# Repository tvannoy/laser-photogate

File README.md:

# Laser photogate

This is a laser photogate timing system, designed primarily for Science Olympiad events such as Wheeled Vehicle, Battery Buggy, Gravity Vehicle, etc.

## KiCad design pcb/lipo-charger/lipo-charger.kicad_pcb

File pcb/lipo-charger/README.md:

# Laser power supply hardware

[The KiCAD design files can be viewed online using KiCanvas.](https://kicanvas.org/?github=https%3A%2F%2Fgithub.com%2Ftvannoy%2Flaser-photogate%2Ftree%2Fhardware%2Fpcb%2Flipo-charger)

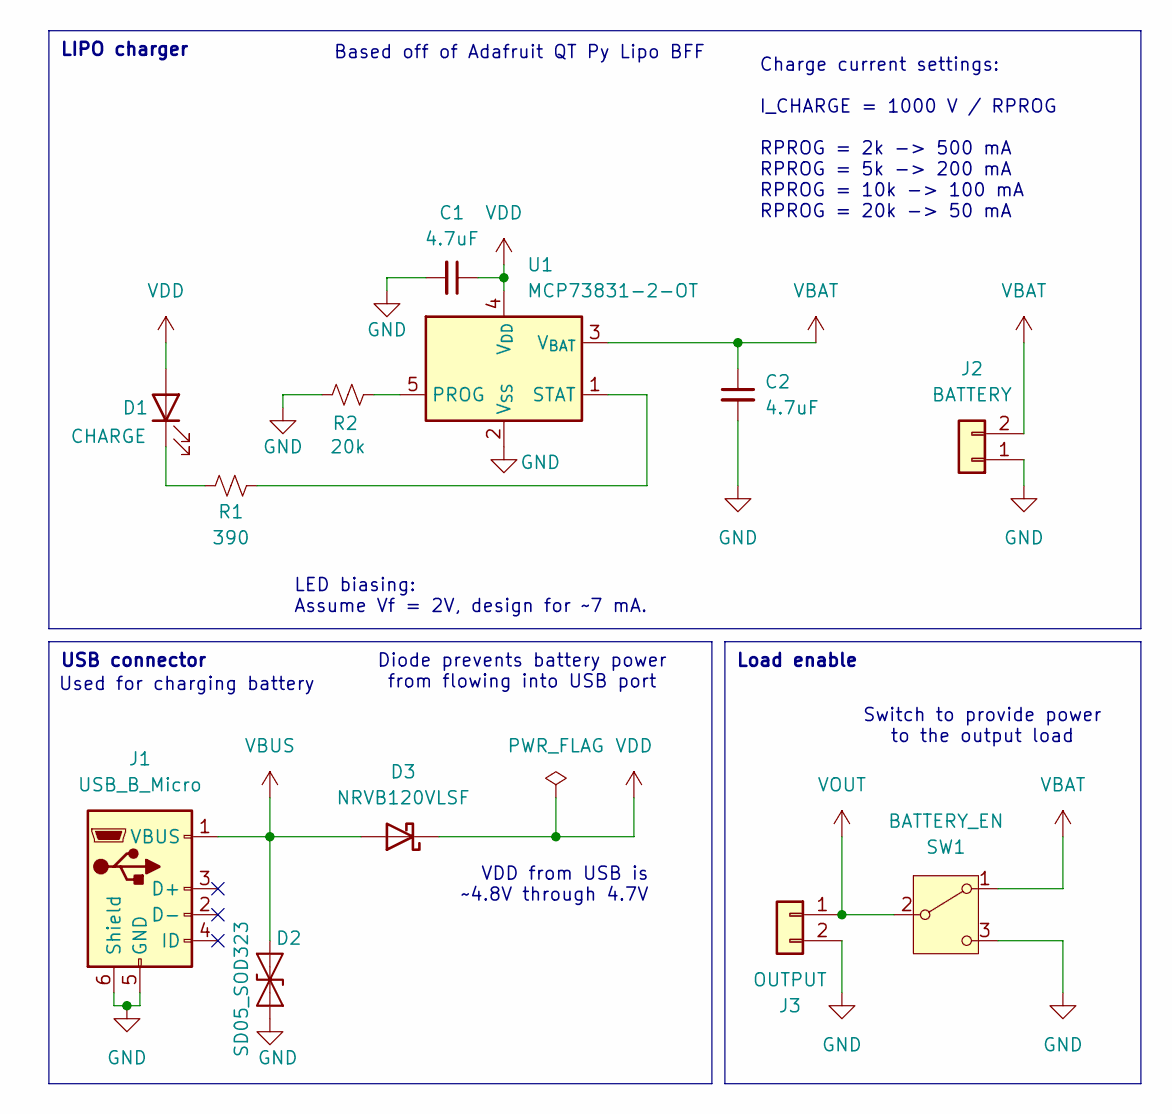
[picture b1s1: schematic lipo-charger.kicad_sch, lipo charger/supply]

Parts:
C1, C2: 4.7uF; C_0805_2012Metric_Pad1.18x1.45mm_HandSolder; Part Number CC0805KKX7R6BB475; JLC 0805
D1: CHARGE; LED_1206_3216Metric_Pad1.42x1.75mm_HandSolder; Part Number B1591UY--20C000112U1930; JLC 1206
D2: SD05_SOD323; D_SOD-323; Part Number Leiditech SD05; JLC SOD-323
D3: NRVB120VLSF; D_SOD-123F; Part Number SM5817PL-TP; JLC SOD-123FL
J1: USB_B_Micro; USB_Micro-B_Wuerth_629105150521; Part Number 629105150521
J2: BATTERY; JST_PH_B2B-PH-K_1x02_P2.00mm_Vertical; Part Number B2B-PH-K-S; JLCSC Part # C5251182
J3: OUTPUT; JST_PH_B2B-PH-K_1x02_P2.00mm_Vertical; Part Number B2B-PH-K-S; JLCSC Part # C5251182
R1: 390; R_0805_2012Metric_Pad1.20x1.40mm_HandSolder; Part Number RC0805FR-07390RL; JLC 0805
R2: 20k; R_0805_2012Metric_Pad1.20x1.40mm_HandSolder; Part Number RC0805FR-0720KL; JLC 0805
SW1: BATTERY_EN; SW_E-Switch_EG1224_SPDT_Angled; Part Number EG1224; JLCSC Part # C273395
U1: MCP73831-2-OT; SOT-23-5; Part Number MCP73831T-2ACI/OT; JLC SOT-23-5

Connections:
GND: C1.2, C2.2, D2.2 (A2), J1.5 (GND), J1.6 (Shield), J2.1, J3.2, R2.2, SW1.3 (C), U1.2 (V_{SS})
unnamed: D1.1 (K), R1.1
unnamed: R2.1, U1.5 (PROG)
unnamed: R1.2, U1.1 (STAT)
VBAT: C2.1, J2.2, SW1.1 (A), U1.3 (V_{BAT})
VBUS: D2.1 (A1), D3.2 (A), J1.1 (VBUS)
VDD: C1.1, D1.2 (A), D3.1 (K), U1.4 (V_{DD})
VOUT: J3.1, SW1.2 (B)

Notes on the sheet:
Load enable
USB connector
LIPO charger
VDD from USB is ~4.8V through 4.7V
Based off of Adafruit QT Py Lipo BFF
Charge current settings: I_CHARGE = 1000 V / RPROG RPROG = 2k -> 500 mA RPROG = 5k -> 200 mA RPROG = 10k -> 100 mA RPROG = 20k -> 50 mA
Diode prevents battery power from flowing into USB port
Used for charging battery
LED biasing: Assume Vf = 2V, design for ~7 mA.
Switch to provide power to the output load

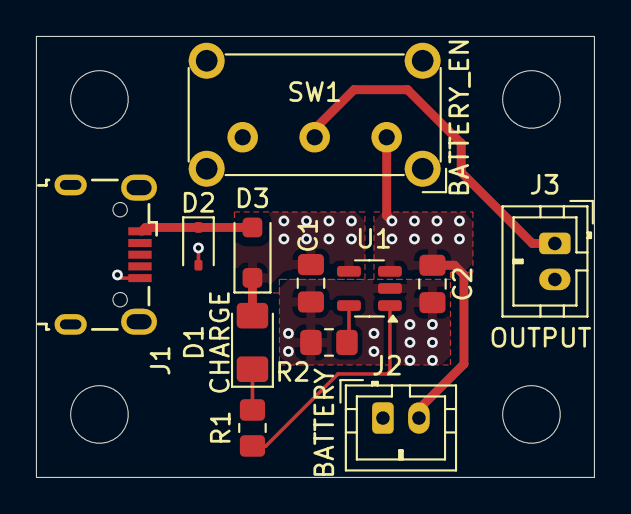
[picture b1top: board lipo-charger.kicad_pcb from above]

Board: 2 copper layers, 31.0 x 24.5 mm, 12 parts (0 on the bottom side), 8 nets.

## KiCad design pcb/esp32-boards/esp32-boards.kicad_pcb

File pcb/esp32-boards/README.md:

# ESP32 wireless photogate hardware

[The KiCAD design files can be viewed online using KiCanvas.](https://kicanvas.org/?github=https%3A%2F%2Fgithub.com%2Ftvannoy%2Flaser-photogate%2Ftree%2Fhardware%2Fpcb%2Fesp32-boards)

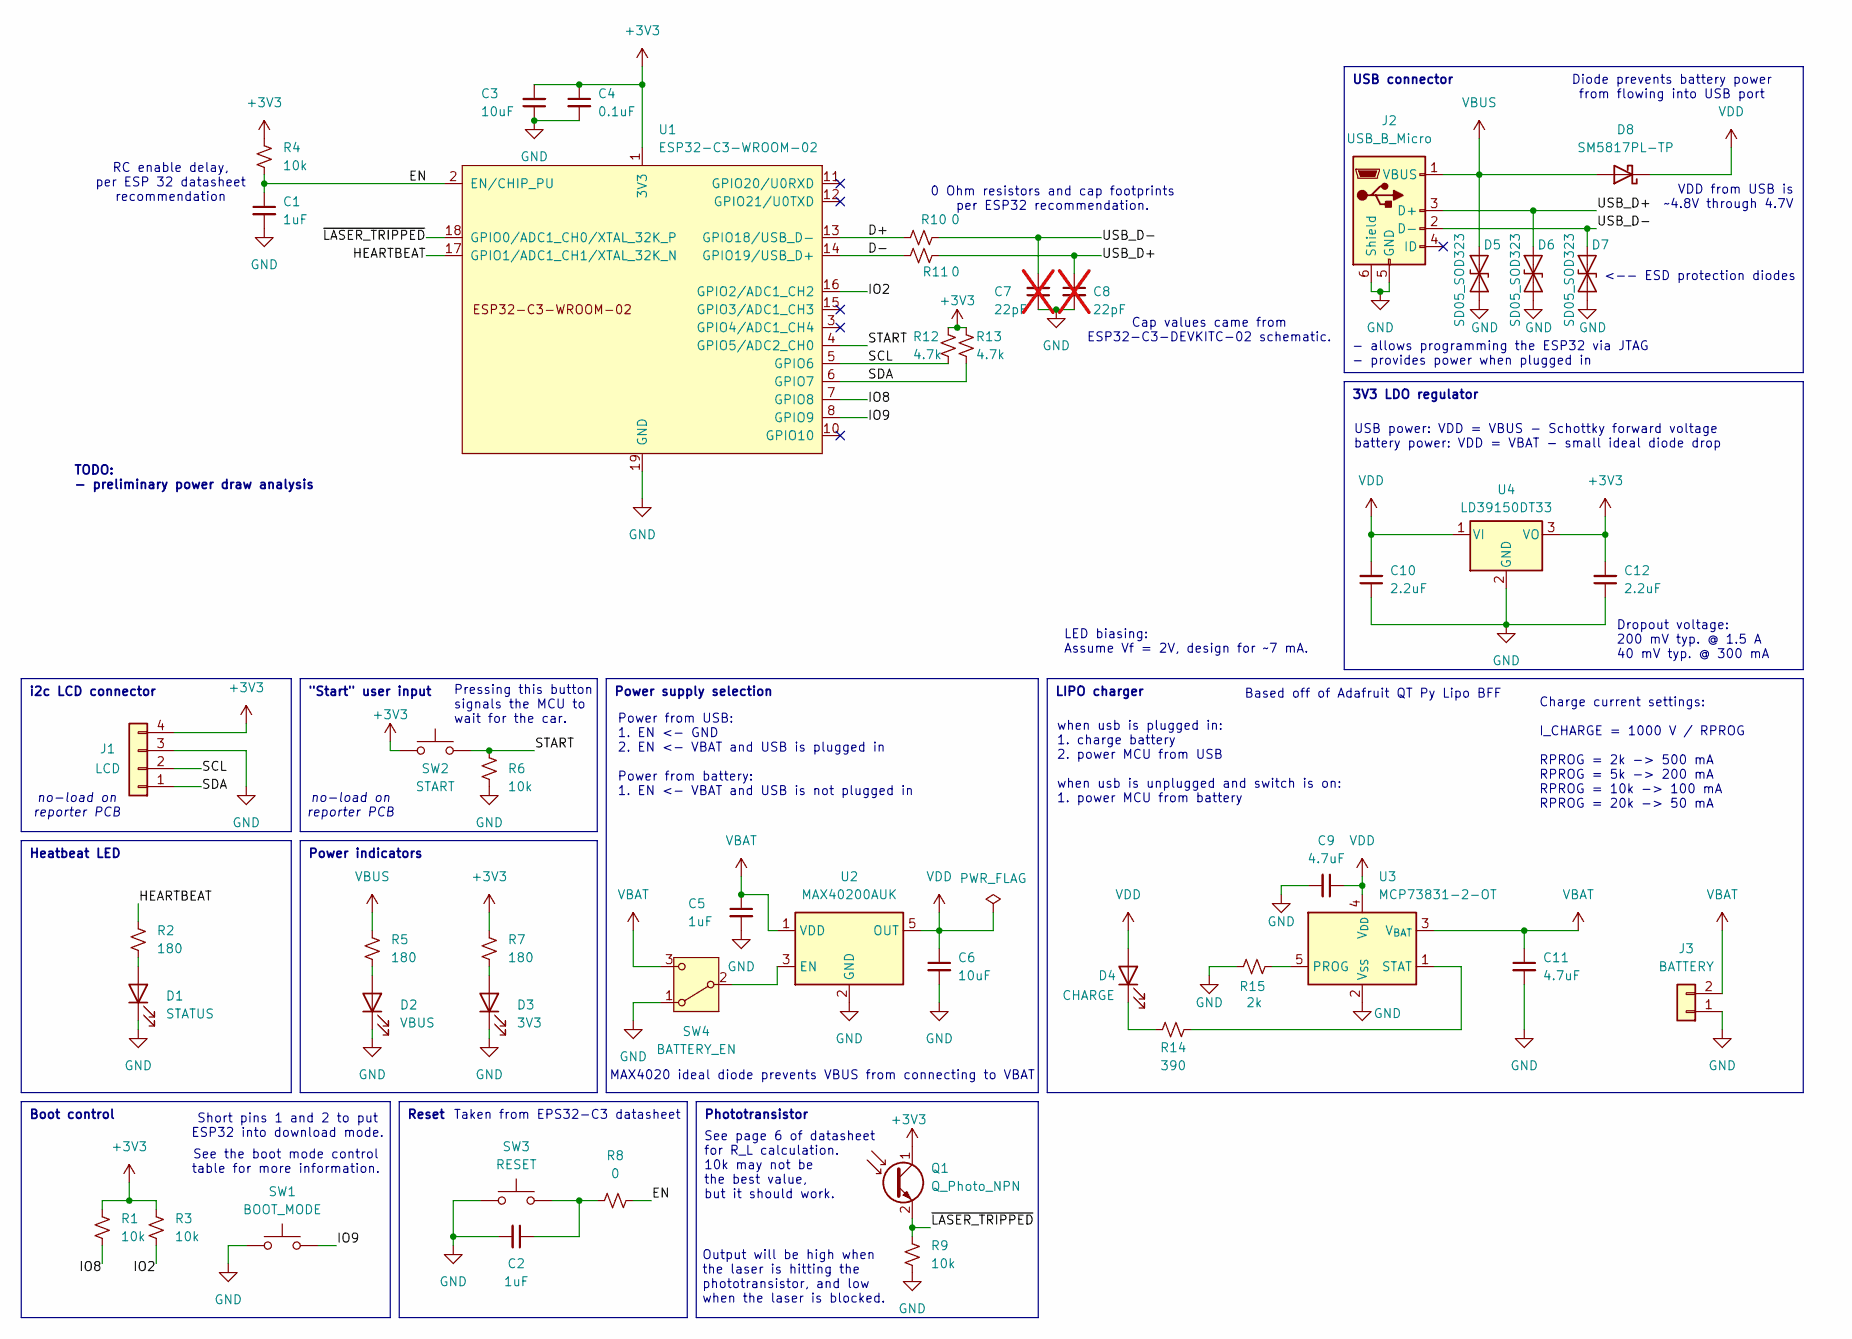
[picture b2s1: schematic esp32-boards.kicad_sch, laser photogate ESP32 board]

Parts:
C1, C2, C5: 1uF; C_0805_2012Metric_Pad1.18x1.45mm_HandSolder; Part Number CC0805KFX7R6BB106; JLC 0805
C3, C6: 10uF; C_0805_2012Metric_Pad1.18x1.45mm_HandSolder; Part Number CC0805KKX7R6BB105; JLC 0805
C4: 0.1uF; C_0805_2012Metric_Pad1.18x1.45mm_HandSolder; Part Number CC0805KRX7R6BB104; JLC 0805
C7, C8: 22pF; C_0805_2012Metric_Pad1.18x1.45mm_HandSolder; Part Number CC0805JRNPO9BN220; JLC 0805; not fitted
C9, C11: 4.7uF; C_0805_2012Metric_Pad1.18x1.45mm_HandSolder; Part Number CC0805KKX7R6BB475; JLC 0805
C10, C12: 2.2uF; C_0805_2012Metric_Pad1.18x1.45mm_HandSolder; Part Number CC0805KKX7R6BB225; JLC 0805
D1: STATUS; LED_1206_3216Metric_Pad1.42x1.75mm_HandSolder; Part Number B1591UY--20C000112U1930; JLC 1206
D2: VBUS; LED_1206_3216Metric_Pad1.42x1.75mm_HandSolder; Part Number B1591UY--20C000112U1930; JLC 1206
D3: 3V3; LED_1206_3216Metric_Pad1.42x1.75mm_HandSolder; Part Number B1591UY--20C000112U1930; JLC 1206
D4: CHARGE; LED_1206_3216Metric_Pad1.42x1.75mm_HandSolder; Part Number B1591UY--20C000112U1930; JLC 1206
D5, D6, D7: SD05_SOD323; D_SOD-323; Part Number Leiditech SD05; JLC SD-323
D8: SM5817PL-TP; D_SOD-123F; Part Number SM5817PL-TP; JLC SOD-123FL
J1: LCD; JST_PH_B4B-PH-K_1x04_P2.00mm_Vertical; Part Number B4B-PH-K-S; JLCSC C131334
J2: USB_B_Micro; USB_Micro-B_Wuerth_629105150521; Part Number 629105150521
J3: BATTERY; JST_PH_B2B-PH-K_1x02_P2.00mm_Vertical; Part Number B2B-PH-K-S; JLCSC C5251182
Q1: Q_Photo_NPN; LED_D3.0mm_Clear; Part Number ALS-PT204-6C/L177; JLCSC C2936540
R1, R3, R4, R6, R9: 10k; R_0805_2012Metric_Pad1.20x1.40mm_HandSolder; Part Number RC0805FR-0710KL; JLC 0805
R2, R5, R7: 180; R_0805_2012Metric_Pad1.20x1.40mm_HandSolder; Part Number RC0805FR-07180RL; JLC 0805
R8, R10, R11: 0; R_0805_2012Metric_Pad1.20x1.40mm_HandSolder; Part Number RC0805JR-070RL; JLC 0805
R12, R13: 4.7k; R_0805_2012Metric_Pad1.20x1.40mm_HandSolder; Part Number RC0805FR-074K7L; JLC 0805
R14: 390; R_0805_2012Metric_Pad1.20x1.40mm_HandSolder; Part Number RC0805FR-07390RL; JLC 0805
R15: 2k; R_0805_2012Metric_Pad1.20x1.40mm_HandSolder; Part Number RC0805FR-072KL; JLC 0805
SW1: BOOT_MODE; SW_PUSH_6mm_H4.3mm; Part Number TS02-66-43-BK-260-LCR-D
SW2: START; JST_PH_B2B-PH-K_1x02_P2.00mm_Vertical; Part Number B2B-PH-K-S; JLCSC C5251182
SW3: RESET; SW_PUSH_6mm_H4.3mm; Part Number TS02-66-43-BK-260-LCR-D
SW4: BATTERY_EN; SW_E-Switch_EG1224_SPDT_Angled; Part Number EG1224; JLCSC C273395
U1: ESP32-C3-WROOM-02; Part Number ESP32-C3-WROOM-02-N4; JLC VFQFN-32-EP
U2: MAX40200AUK; SOT-23-5; Part Number MAX40200AUK+T; JLC SOT-23-5
U3: MCP73831-2-OT; SOT-23-5; Part Number MCP73831T-2ACI/OT; JLC SOT-23-5
U4: LD39150DT33; TO-252-3_TabPin2; Part Number LD39150DT33-R; JLC TO-252

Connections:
+3V3: C3.2, C4.1, C12.2, J1.4, Q1.1 (C), R1.2, R3.2, R4.2, R7.1, R12.1, R13.1, SW2.1, U1.1 (3V3), U4.3 (VO)
/D+: R10.1, U1.13 (GPIO18/USB_D-)
/D-: R11.1, U1.14 (GPIO19/USB_D+)
/EN: C1.1, R4.1, R8.2, U1.2 (EN/CHIP_PU)
/HEARTBEAT: R2.1, U1.17 (GPIO1/ADC1_CH1/XTAL_32K_N)
/IO2: R3.1, U1.16 (GPIO2/ADC1_CH2)
/IO8: R1.1, U1.7 (GPIO8)
/IO9: SW1.2, U1.8 (GPIO9)
/SCL: J1.2, R12.2, U1.5 (GPIO6)
/SDA: J1.1, R13.2, U1.6 (GPIO7)
/START: R6.1, SW2.2, U1.4 (GPIO5/ADC2_CH0)
/USB_D+: C8.1, D6.1 (A1), J2.3 (D+), R11.2
/USB_D-: C7.2, D7.1 (A1), J2.2 (D-), R10.2
/~LASER_TRIPPED: Q1.2 (E), R9.1, U1.18 (GPIO0/ADC1_CH0/XTAL_32K_P)
GND: C1.2, C2.2, C3.1, C4.2, C5.2, C6.2, C7.1, C8.2, C9.2, C10.1, C11.2, C12.1, D1.1 (K), D2.1 (K), D3.1 (K), D5.2 (A2), D6.2 (A2), D7.2 (A2), J1.3, J2.5 (GND), J2.6 (Shield), J3.1, R6.2, R9.2, R15.2, SW1.1, SW3.1, SW4.1 (A), U1.9 (GND), U1.19 (GND), U2.2 (GND), U3.2 (V_{SS}), U4.2 (GND)
unnamed: C2.1, R8.1, SW3.2
unnamed: D1.2 (A), R2.2
unnamed: D2.2 (A), R5.2
unnamed: D3.2 (A), R7.2
unnamed: D4.1 (K), R14.1
unnamed: SW4.2 (B), U2.3 (EN)
unnamed: R15.1, U3.5 (PROG)
unnamed: R14.2, U3.1 (STAT)
VBAT: C5.1, C11.1, J3.2, SW4.3 (C), U2.1 (VDD), U3.3 (V_{BAT})
VBUS: D5.1 (A1), D8.2 (A), J2.1 (VBUS), R5.1
VDD: C6.1, C9.1, C10.2, D4.2 (A), D8.1 (K), U2.5 (OUT), U3.4 (V_{DD}), U4.1 (VI)

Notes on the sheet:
Heatbeat LED
Boot control
"Start" user input
Power indicators
Reset
USB connector
i2c LCD connector
Phototransistor
LIPO charger
3V3 LDO regulator
Power supply selection
Short pins 1 and 2 to put ESP32 into download mode.
Dropout voltage: 200 mV typ. @ 1.5 A 40 mV typ. @ 300 mA
when usb is plugged in: 1. charge battery 2. power MCU from USB when usb is unplugged and switch is on: 1. power MCU from battery
VDD from USB is ~4.8V through 4.7V
- allows programming the ESP32 via JTAG - provides power when plugged in
Based off of Adafruit QT Py Lipo BFF
Diode prevents battery power from flowing into USB port
0 Ohm resistors and cap footprints per ESP32 recommendation.
TODO: - preliminary power draw analysis
Power from USB: 1. EN <- GND 2. EN <- VBAT and USB is plugged in Power from battery: 1. EN <- VBAT and USB is not plugged in
no-load on reporter PCB
Output will be high when the laser is hitting the phototransistor, and low when the laser is blocked.
Pressing this button signals the MCU to wait for the car.
See page 6 of datasheet for R_L calculation. 10k may not be the best value, but it should work.
See the boot mode control table for more information.
MAX4020 ideal diode prevents VBUS from connecting to VBAT
Taken from EPS32-C3 datasheet
USB power: VDD = VBUS - Schottky forward voltage battery power: VDD = VBAT - small ideal diode drop
LED biasing: Assume Vf = 2V, design for ~7 mA.
Charge current settings: I_CHARGE = 1000 V / RPROG RPROG = 2k -> 500 mA RPROG = 5k -> 200 mA RPROG = 10k -> 100 mA RPROG = 20k -> 50 mA
RC enable delay, per ESP 32 datasheet recommendation
Cap values came from ESP32-C3-DEVKITC-02 schematic.
<-- ESD protection diodes

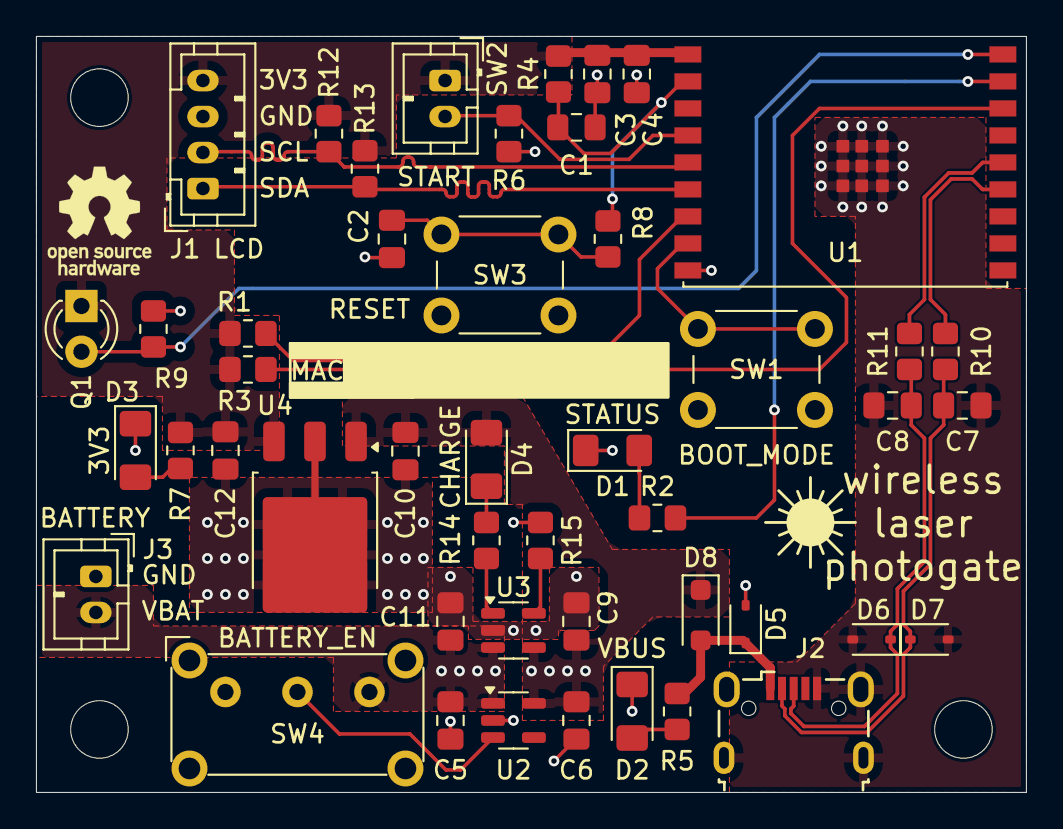
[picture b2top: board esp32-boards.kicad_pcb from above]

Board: 2 copper layers, 55.0 x 42.0 mm, 48 parts (0 on the bottom side), 26 nets.

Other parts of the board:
svg2mod: G***; laser

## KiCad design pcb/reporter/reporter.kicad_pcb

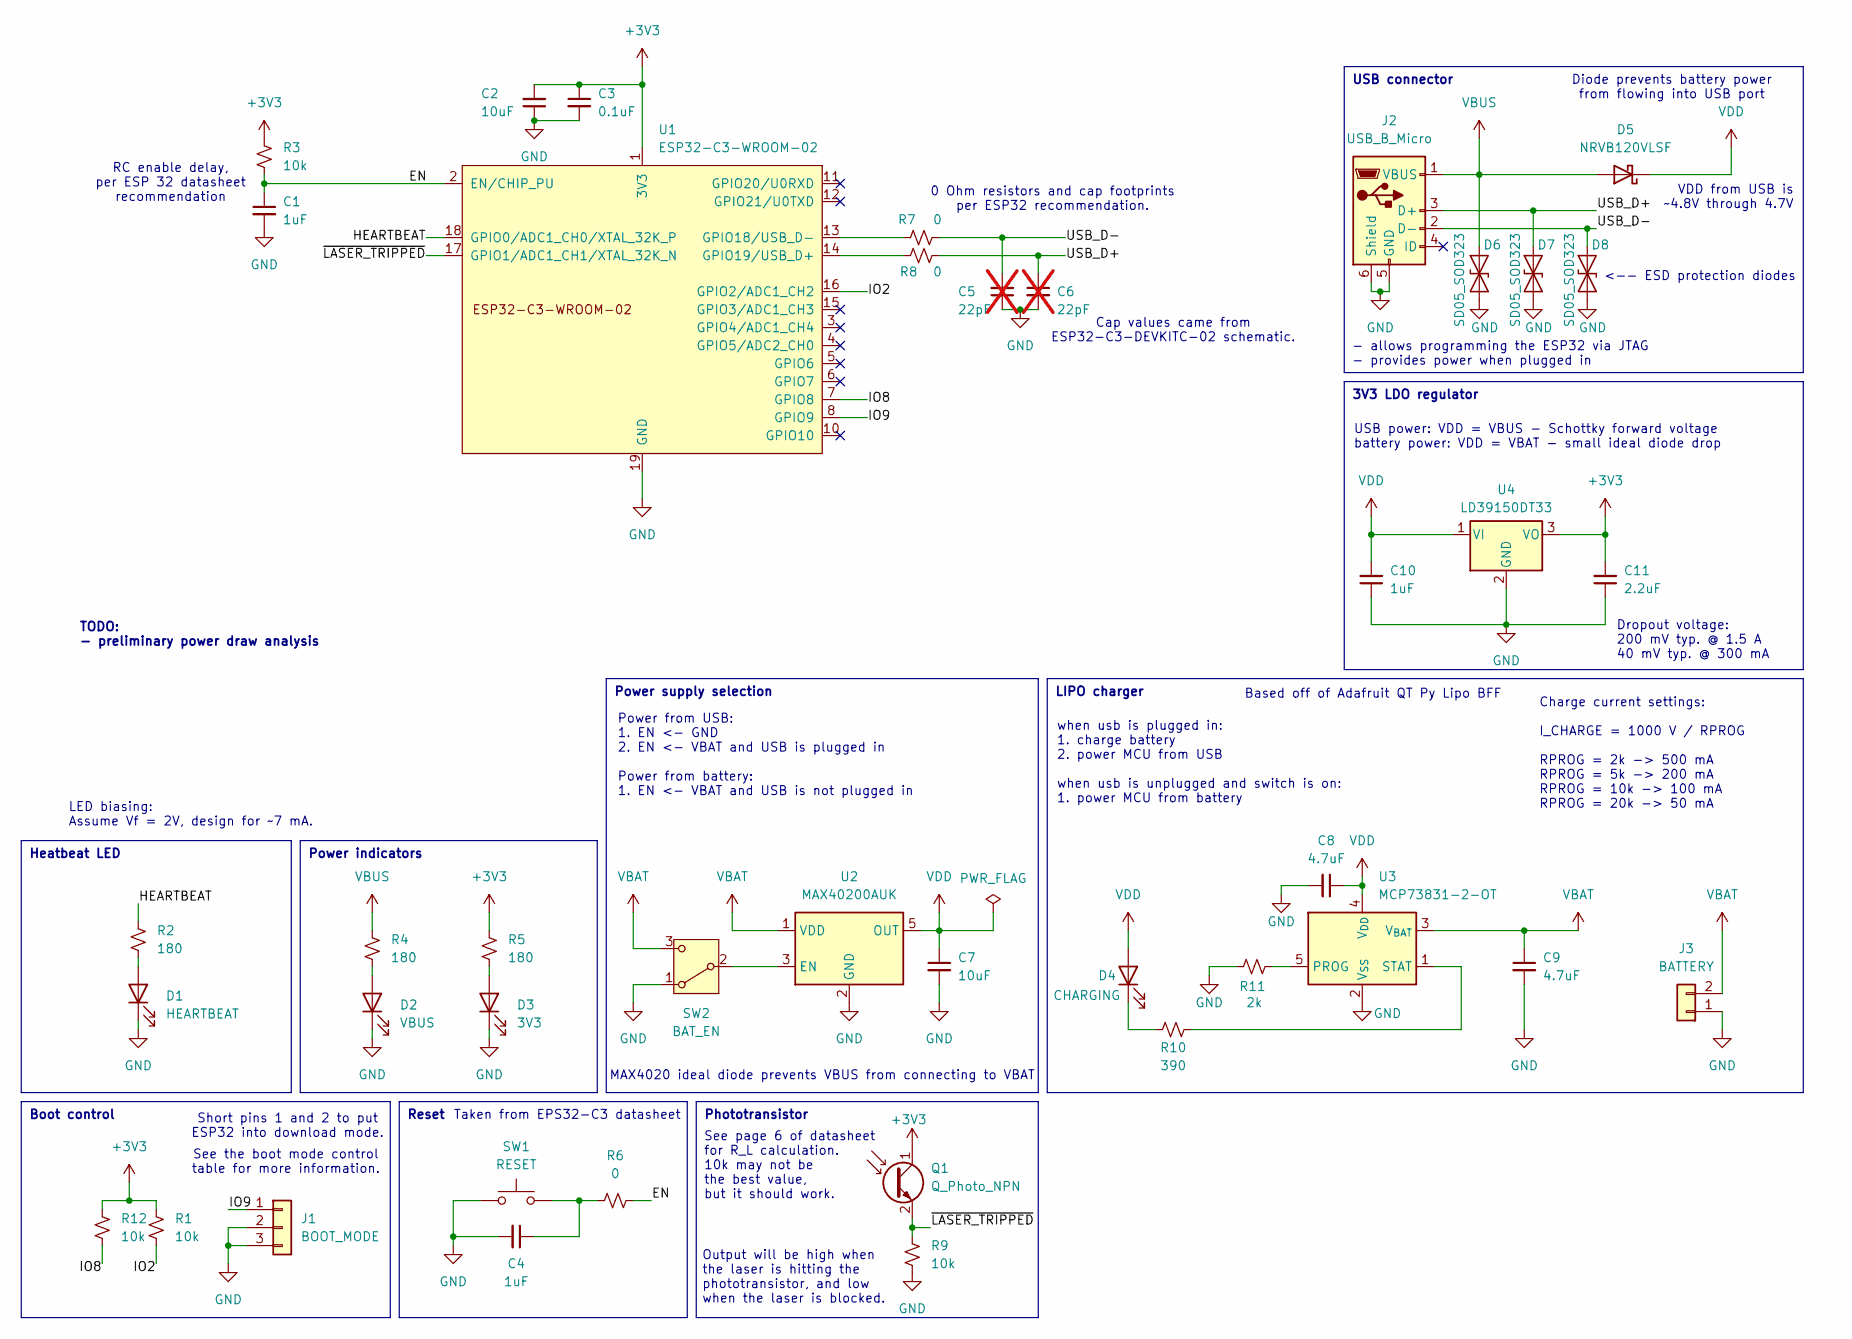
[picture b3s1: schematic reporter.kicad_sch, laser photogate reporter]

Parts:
C1, C4, C10: 1uF; C_1206_3216Metric_Pad1.33x1.80mm_HandSolder
C2, C7: 10uF; C_1206_3216Metric_Pad1.33x1.80mm_HandSolder
C3: 0.1uF; C_1206_3216Metric_Pad1.33x1.80mm_HandSolder
C5, C6: 22pF; C_1206_3216Metric_Pad1.33x1.80mm_HandSolder; not fitted
C8, C9: 4.7uF; C_1206_3216Metric_Pad1.33x1.80mm_HandSolder
C11: 2.2uF; C_1206_3216Metric_Pad1.33x1.80mm_HandSolder
D1: HEARTBEAT; LED_1206_3216Metric_Pad1.42x1.75mm_HandSolder; Part Number B1591UY--20C000112U1930
D2: VBUS; LED_1206_3216Metric_Pad1.42x1.75mm_HandSolder; Part Number B1591UY--20C000112U1930
D3: 3V3; LED_1206_3216Metric_Pad1.42x1.75mm_HandSolder; Part Number B1591UY--20C000112U1930
D4: CHARGING; LED_1206_3216Metric_Pad1.42x1.75mm_HandSolder; Part Number B1591UY--20C000112U1930
D5: NRVB120VLSF; D_SOD-123F; Part Number NRVB120VLSF
D6, D7, D8: SD05_SOD323; D_SOD-323; Part Number SD05C-7
J1: BOOT_MODE; PinHeader_1x03_P2.54mm_Vertical
J2: USB_B_Micro; USB_Micro-B_Wuerth_629105150521; Part Number 629105150521
J3: BATTERY; JST_PH_B2B-PH-K_1x02_P2.00mm_Vertical; Part Number B2B-XH-A
Q1: Q_Photo_NPN; LED_D3.0mm_Clear; Part Number ALS-PT204-6C/L177
R1, R3, R9, R12: 10k; R_1206_3216Metric_Pad1.30x1.75mm_HandSolder
R2, R4, R5: 180; R_1206_3216Metric_Pad1.30x1.75mm_HandSolder
R6, R7, R8: 0; R_1206_3216Metric_Pad1.30x1.75mm_HandSolder
R10: 390; R_1206_3216Metric_Pad1.30x1.75mm_HandSolder
R11: 2k; R_1206_3216Metric_Pad1.30x1.75mm_HandSolder
SW1: RESET; SW_PUSH_6mm_H4.3mm; Part Number TS02-66-43-BK-260-LCR-D
SW2: BAT_EN; SW_E-Switch_EG1224_SPDT_Angled; Part Number EG1224
U1: ESP32-C3-WROOM-02; Part Number ESP32-C3-WROOM-02-N4
U2: MAX40200AUK; SOT-23-5; Part Number MAX40200AUK+T
U3: MCP73831-2-OT; SOT-23-5; Part Number MCP73831T-2ACI/OT
U4: LD39150DT33; TO-252-3_TabPin2; Part Number LD39150DT33-R

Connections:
+3V3: C2.2, C3.1, C11.2, Q1.1 (C), R1.2, R3.2, R5.1, R12.2, U1.1 (3V3), U4.3 (VO)
/EN: C1.1, R3.1, R6.2, U1.2 (EN/CHIP_PU)
/HEARTBEAT: R2.1, U1.18 (GPIO0/ADC1_CH0/XTAL_32K_P)
/IO2: R1.1, U1.16 (GPIO2/ADC1_CH2)
/IO8: R12.1, U1.7 (GPIO8)
/IO9: J1.1, U1.8 (GPIO9)
/USB_D+: C6.1, D7.1 (A1), J2.3 (D+), R8.2
/USB_D-: C5.2, D8.1 (A1), J2.2 (D-), R7.2
/~LASER_TRIPPED: Q1.2 (E), R9.1, U1.17 (GPIO1/ADC1_CH1/XTAL_32K_N)
GND: C1.2, C2.1, C3.2, C4.2, C5.1, C6.2, C7.2, C8.2, C9.2, C10.1, C11.1, D1.1 (K), D2.1 (K), D3.1 (K), D6.2 (A2), D7.2 (A2), D8.2 (A2), J1.2, J1.3, J2.5 (GND), J2.6 (Shield), J3.1, R9.2, R11.2, SW1.1, SW2.1 (A), U1.9 (GND), U1.19 (GND), U2.2 (GND), U3.2 (V_{SS}), U4.2 (GND)
unnamed: C4.1, R6.1, SW1.2
unnamed: D1.2 (A), R2.2
unnamed: D2.2 (A), R4.2
unnamed: D3.2 (A), R5.2
unnamed: D4.1 (K), R10.1
unnamed: SW2.2 (B), U2.3 (EN)
unnamed: R7.1, U1.13 (GPIO18/USB_D-)
unnamed: R8.1, U1.14 (GPIO19/USB_D+)
unnamed: R11.1, U3.5 (PROG)
unnamed: R10.2, U3.1 (STAT)
VBAT: C9.1, J3.2, SW2.3 (C), U2.1 (VDD), U3.3 (V_{BAT})
VBUS: D5.2 (A), D6.1 (A1), J2.1 (VBUS), R4.1
VDD: C7.1, C8.1, C10.2, D4.2 (A), D5.1 (K), U2.5 (OUT), U3.4 (V_{DD}), U4.1 (VI)

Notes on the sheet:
Heatbeat LED
Boot control
Power indicators
Reset
USB connector
Phototransistor
LIPO charger
3V3 LDO regulator
Power supply selection
Short pins 1 and 2 to put ESP32 into download mode.
Dropout voltage: 200 mV typ. @ 1.5 A 40 mV typ. @ 300 mA
when usb is plugged in: 1. charge battery 2. power MCU from USB when usb is unplugged and switch is on: 1. power MCU from battery
VDD from USB is ~4.8V through 4.7V
- allows programming the ESP32 via JTAG - provides power when plugged in
Based off of Adafruit QT Py Lipo BFF
Diode prevents battery power from flowing into USB port
0 Ohm resistors and cap footprints per ESP32 recommendation.
TODO: - preliminary power draw analysis
Power from USB: 1. EN <- GND 2. EN <- VBAT and USB is plugged in Power from battery: 1. EN <- VBAT and USB is not plugged in
Output will be high when the laser is hitting the phototransistor, and low when the laser is blocked.
See page 6 of datasheet for R_L calculation. 10k may not be the best value, but it should work.
See the boot mode control table for more information.
MAX4020 ideal diode prevents VBUS from connecting to VBAT
Taken from EPS32-C3 datasheet
USB power: VDD = VBUS - Schottky forward voltage battery power: VDD = VBAT - small ideal diode drop
LED biasing: Assume Vf = 2V, design for ~7 mA.
Charge current settings: I_CHARGE = 1000 V / RPROG RPROG = 2k -> 500 mA RPROG = 5k -> 200 mA RPROG = 10k -> 100 mA RPROG = 20k -> 50 mA
RC enable delay, per ESP 32 datasheet recommendation
Cap values came from ESP32-C3-DEVKITC-02 schematic.
<-- ESD protection diodes

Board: 2 copper layers, 41 parts (0 on the bottom side), 23 nets, no tracks yet.

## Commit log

2024-03-26 add kicad gitignore template
2024-03-26 add README
2024-03-26 document high-level system design
2024-03-26 ignore .DS_Store
2024-03-26 try getting dark-mode for svg
2024-03-26 add figure caption
2024-03-26 remove figurecaption; didn't look good
2024-03-26 add high-level state diagrams
2024-03-26 remove flexbox because github doesn't support inline style
2024-03-26 add reporter schematic
2024-03-26 add link to KiCanvas viewer
2024-03-27 replace ESD diodes with larger package
2024-03-27 use USB connector with board guides
2024-03-27 place components in preliminary locations
    This is just the initial component placement. Some changes will
    inevitably happen.
2024-03-27 rename reporter to a generic name
    The same PCB can be used for the reporter and controller. They are
    essentially the same, except the controller will have a few more
    components. These components can be no-loaded for the reporter.
2024-03-28 add LCD and start button
2024-03-28 switch to 0805 for most components
2024-03-28 update battery switch name
2024-03-29 finish first draft of layout
2024-03-29 add screenshot of differential impedance calculation
2024-03-29 update reference designators
2024-03-29 add documentation; move board; resize VBAT pour
2024-03-30 add usb connector 3d model
2024-03-30 create laser graphic
2024-03-30 add final touches on silkscreen
2024-03-30 add project-based footprint library
2024-03-30 set up DRC and fix DRC errors
2024-03-30 finish drc
2024-03-30 create circuit for charging lipo and powering laser
2024-03-30 set grid origin
2024-03-30 update kicanvas links in READMEs
2024-03-31 update BOMs for JLC assembly
2024-03-31 add tooling holes for assembly
    https://jlcpcb.com/help/article/47-How-to-add-tooling-holes-for-PCB-assembly-order
2024-03-31 remove tooling holes; finalize for production
    It's easier to have JLC add the tooling holes.
2024-04-01 add download script and links to datasheets
    I'd like to keep all the datasheets alongside the repository, but
    don't want to track them in git.
2024-04-01 remove stray )
2024-04-07 create solidworks assembly for esp32 PCB
    Solidworks didn't like directly using the step file in the main assembly, so I made a subassembly that just has the pcb step file in it; that subassembly behaves better in the main assembly file.
2024-04-07 create initial design for bottom of enclosure
2024-04-07 add 3d models for lcd, switch, and lens
2024-04-07 convert third party components to solidworks assemblies
2024-04-07 change enclosure shape to accommodate lcd
2024-04-07 move pcb and add screw holes in standoffs
2024-04-07 move pcb in from edges to make assembly easier
2024-04-07 cleanup mates; line up lens and place LED at it's focal length
2024-04-07 position lcd; cutout holes for lcd and lens
2024-04-08 add mounting standoffs for lcd
2024-04-08 position pushbutton and add cutout
2024-04-09 add cutouts for power switch and usb
2024-04-09 decrease top thickness so pushbutton will latch in
2024-04-09 add LED spacer for enclosure considerations
    I want the LED to spaced higher off the board so the converging lens in
    the enclosure can be centered on the LED without the board having to be
    so high up in the enclosure. This will make the PCB standoffs shorter
    and give more space for the LCD and pushbutton wiring.
2024-04-09 add LED spacer
    Placing the LED higher off the PCB made it so the PCB doesn't have to be so high and there is more space for the pushbutton and LCD
2024-04-09 fix constraints/mates after adding LED spacer
2024-04-09 reduce top height again
2024-04-09 reduce enclosure height
2024-04-09 fix external references to pcb step files
    for some reason, the pcb subassembly got messed up...
2024-04-09 roll forward to restore mounting holes
2024-04-09 use part instead of assembly for pcb
    For some reason, solidworks was not behaving properly with the pcb subassembly that referenced the step file. The assembly kept reloading the old step file without the led spacer/standoff.
    Importing the step file with 3D interconnect turned off, and saving it as a multibody part seems to be working now; the pcb part doesn't get messed up when I close/reopen the main enclosure assembly,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
2024-04-10 emboss text for button and switch
2024-04-10 add fillets
2024-04-10 remove temp files
2024-04-13 change to M4 set screw for lens
2024-04-13 correct on/off symbol positions
2024-04-13 recess lens and set distance b/t lens and receiever
    The distance between the lens and phototransistor is now equal to the lens' back focal length, which puts the focus point at the phototransistor.
    Lens was recessed fully in the enclosure for safety, etc.
2024-04-13 export STL files
2024-04-13 rename to controller enclosure
    The responder enclosure is the same, just minus the LCD and button
2024-04-13 create enclosure for responder esp32
    Removed the LCD and pushbutton features from the controller enclosure
2024-04-13 add STL for responder enclosure
    The bottom part of the responder enclosure is the same as the bottom for the controller enclosure.
2024-04-13 fix path to USB 3D model
2024-04-13 start enclosure for laser module
    I'm trying to modify the existing esp32 enclosure
2024-04-15 reduce height of lens recess extrusion
    The previous height went all the way to the bottom, which made the top and bottom pieces not mate together properly. Reducing the height avoids this problems and also reduces plastic :smiley:
2024-04-15 make usb cutout larger
    The usb cable didn't fit before.
2024-04-15 make start text larger
2024-04-15 fix power switch cutout
    I also fixed out-of-context external references by renaming controller-enclosure back to esp32-enclosure, fixing everything there, then using "save as" to save the controller-enclosure with update re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
2024-04-15 recreate responder enclosure from latest controller enclosure
    Used "save as" to save the controller-enclosure as the responder-enclosure, then deleted the LCD and pushbutton features.
2024-04-15 update STL files
2024-04-16 design laser enclosure
2024-04-16 add mounting holes and fillet laser cutout
2024-04-16 add laser enclosure STLs
2024-04-16 fix lens height
    the lens height was 50 mm from the bottom edge, not the bottom face, so the 50 mm dimension was actually slightly diagonal.
2024-04-17 increase mounting hole depth; add on/off symbols; decrease usb cutout size
2024-04-17 swap power symbol sides

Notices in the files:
pcb/esp32-boards/esp32-boards.kicad_pcb:
© Trevor Vannoy
SPDX-License-Identifier: CERN-OHL-S-2.0
pcb/lipo-charger/lipo-charger.kicad_pcb:
License: CERN-OHL-S-2.0
